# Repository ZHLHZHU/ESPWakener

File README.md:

## 简介
EspWakener是一个基于Wake-on-LAN协议的网络唤醒器，通过MQTT协议进行控制。

## 配置说明
* 把开关拨到"ON"，通电（顺序不能乱）。连上Wakener发出的热点，进入192.168.8.1（你都看到本页面了，肯定已经完成这些步骤）。
* 进入Config页签，配置好WIFI名和密码、WOL的端口（默认9）。
* 打开MQTT开关，填入MQTT连接（只支持mqtt://协议，不支持TLS和WS），填入Topic。MQTT用户名和密码如果没有可以忽略。
* 点击保存，把开关拨到"1"，断电，通电。（拨开关和断电的顺序任意，因为本设备只会根据通电瞬间的开关状态来判断是否进入配置模式）。
## 协议
### Wakener上线
当Wakener成功连接Mqtt服务器后，会广播一条自身状态的信息
```json
{
    "action": "join",
    "sender": "SwingFrogWakener",
    "deviceName": "SwingFrogWakener",
    "ip": "192.168.1.188",
    "ssid": "WIFI_NAME",
    "rssi": -47,
    "version": "2.0.0"
}
```
### 请求唤醒
向Wakener所配置的Topic发送以下指令，Wakener将会在所在局域网广播唤醒包
MAC地址分隔符支持 ':' 和 '-'
```json
{
    "action": "wake",
    "mac": "a9:a9:59:30:d8:ee"
}
```
### 请求设备状态
向Wakener所配置的Topic发送以下指令，将会返回Wakener当前状态信息
```json
{
    "action": "info"
}
```

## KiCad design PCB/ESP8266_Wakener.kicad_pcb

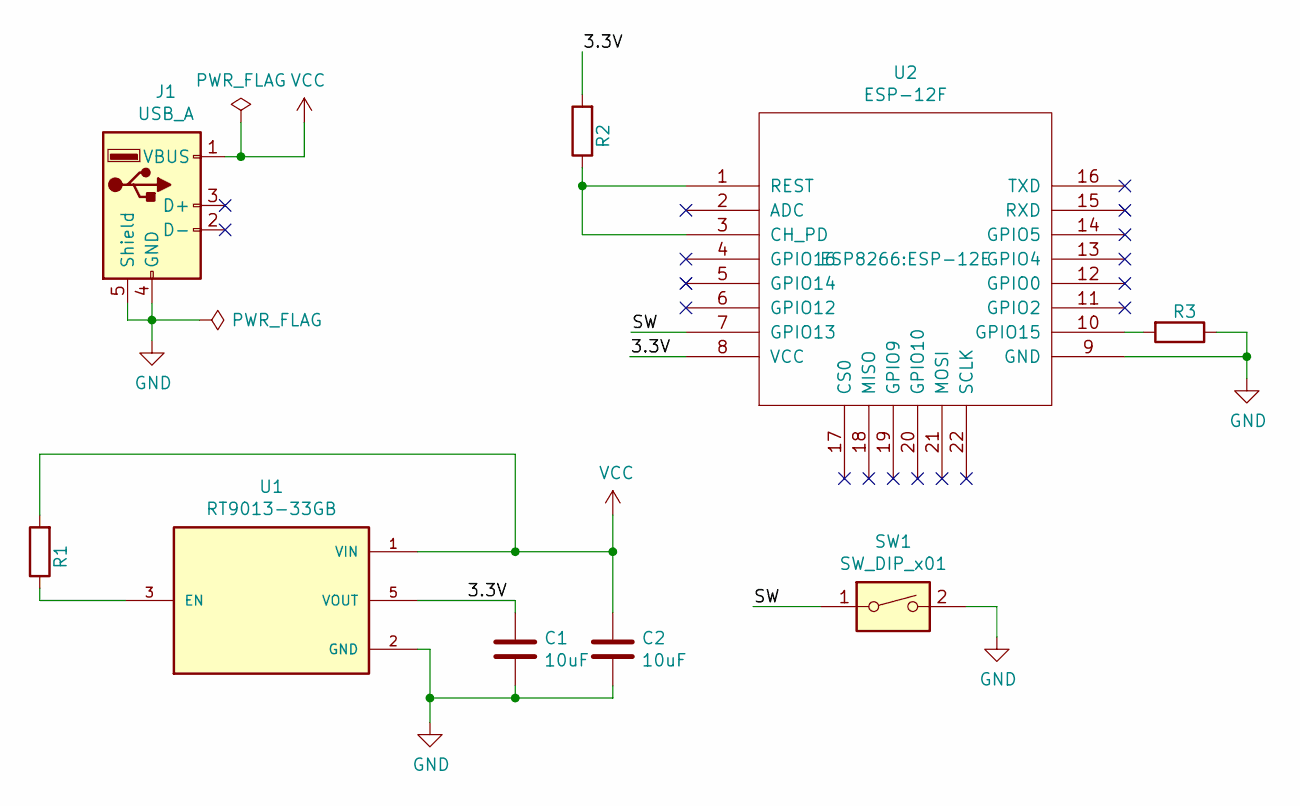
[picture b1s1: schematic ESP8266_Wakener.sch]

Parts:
C1, C2: 10uF; C_0603_1608Metric
J1: USB_A; USB_A_CNCTech_1001-011-01101_Horizontal
R1, R2, R3: 10K; R_0603_1608Metric
SW1: SW_DIP_x01; SW_SMT_1P
U1: RT9013-33GB; SOT-23-5_HandSoldering; PARTREV Aprill 2011
U2: ESP-12F; ESP-12E

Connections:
/3.3V: C1.1, R2.2, U1.5 (VOUT), U2.8 (VCC)
/SW: SW1.1, U2.7 (GPIO13)
GND: C1.2, C2.2, J1.4 (GND), J1.5 (Shield), R3.1, SW1.2, U1.2 (GND), U2.9 (GND)
unnamed: R1.1, U1.3 (EN)
unnamed: R2.1, U2.1 (REST), U2.3 (CH_PD)
unnamed: R3.2, U2.10 (GPIO15)
VCC: C2.1, J1.1 (VBUS), R1.2, U1.1 (VIN)

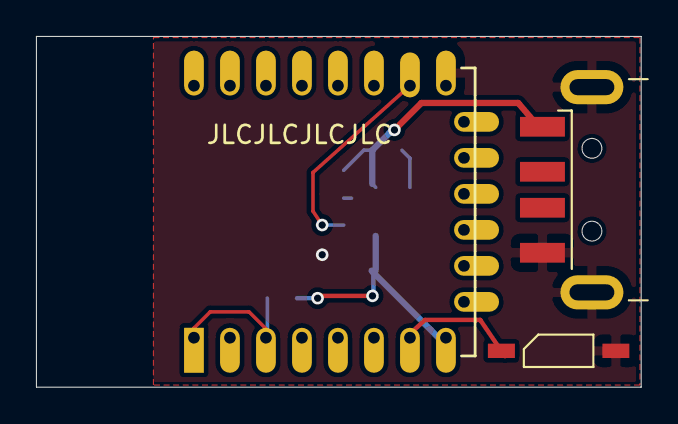
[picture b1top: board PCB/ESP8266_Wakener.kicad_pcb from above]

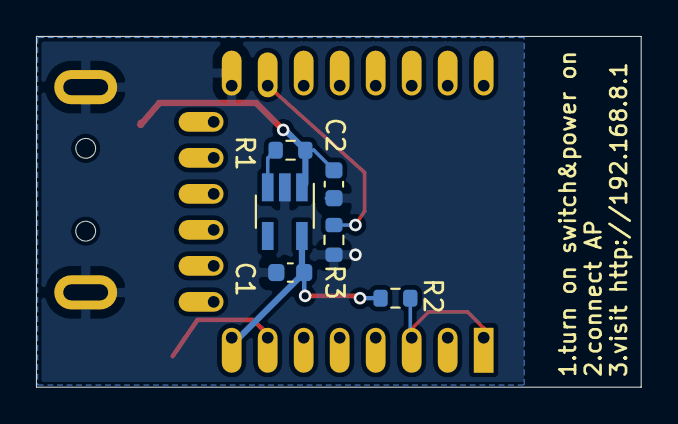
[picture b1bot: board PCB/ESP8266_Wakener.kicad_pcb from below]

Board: 2 copper layers, 33.6 x 19.5 mm, 9 parts (6 on the bottom side), 7 nets.

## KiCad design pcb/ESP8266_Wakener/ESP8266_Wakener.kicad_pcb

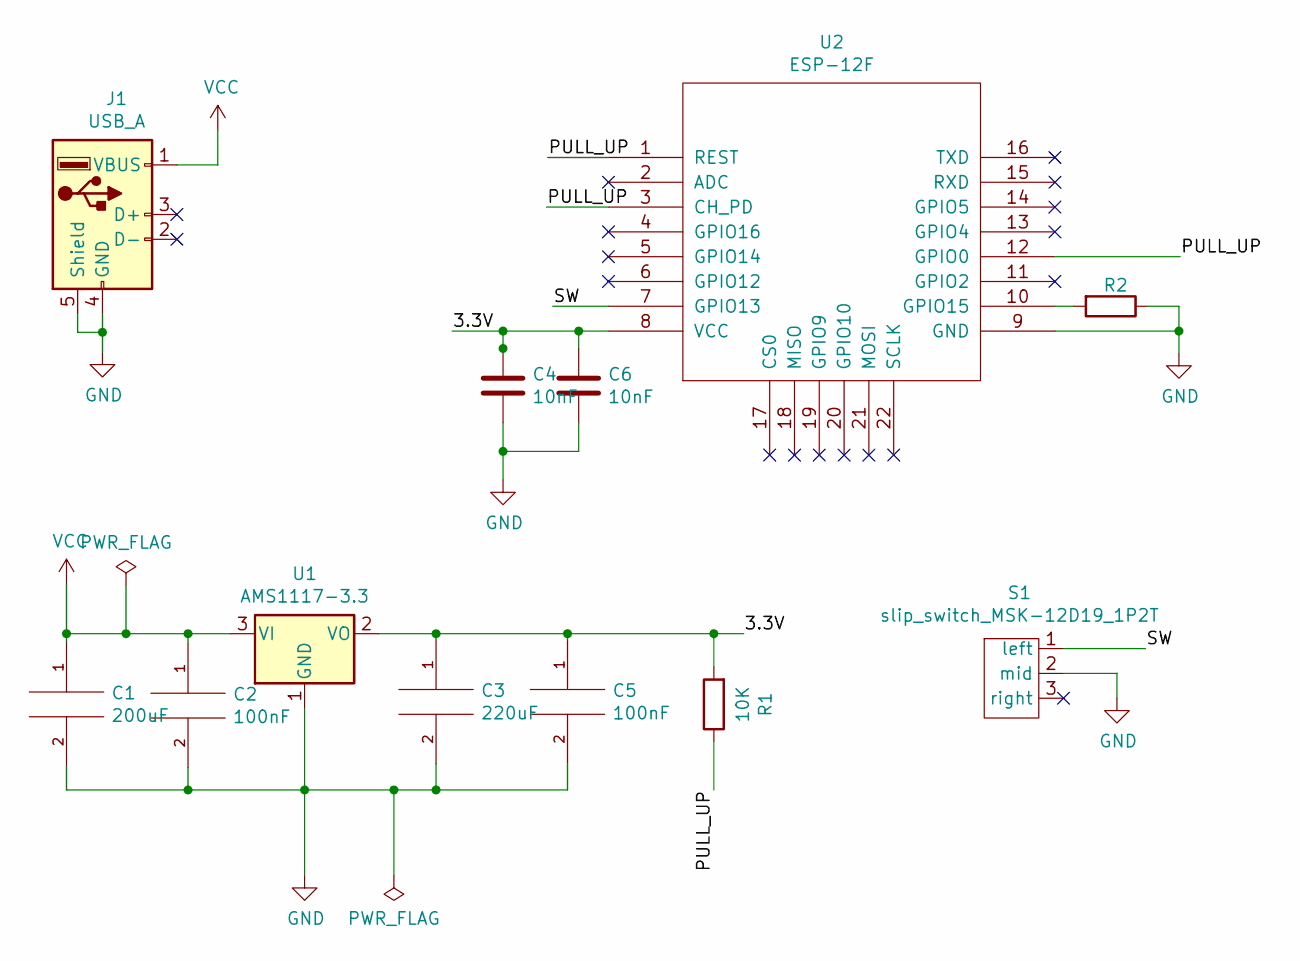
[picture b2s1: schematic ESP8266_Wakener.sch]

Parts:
C1: 200uF; C_0603_1608Metric
C2, C5: 100nF; C_0603_1608Metric
C3: 220uF; C_0603_1608Metric
C4, C6: 10nF; C_0603_1608Metric
J1: USB_A; USB_A_CNCTech_1001-011-01101_Horizontal
R1, R2: 10K; R_0603_1608Metric
S1: slip_switch_MSK-12D19_1P2T; SlipSwitch_MSK-12D19_1P2T
U1: AMS1117-3.3; SOT-223-3_TabPin2
U2: ESP-12F; ESP-12E

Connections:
/3.3V: C3.1, C4.1, C5.1, C6.1, R1.2, U1.2 (VO), U2.8 (VCC)
/PULL_UP: R1.1, U2.1 (REST), U2.3 (CH_PD), U2.12 (GPIO0)
/SW: S1.1 (left), U2.7 (GPIO13)
GND: C1.2, C2.2, C3.2, C4.2, C5.2, C6.2, J1.4 (GND), J1.5 (Shield), R2.1, S1.2 (mid), U1.1 (GND), U2.9 (GND)
unnamed: R2.2, U2.10 (GPIO15)
VCC: C1.1, C2.1, J1.1 (VBUS), U1.3 (VI)

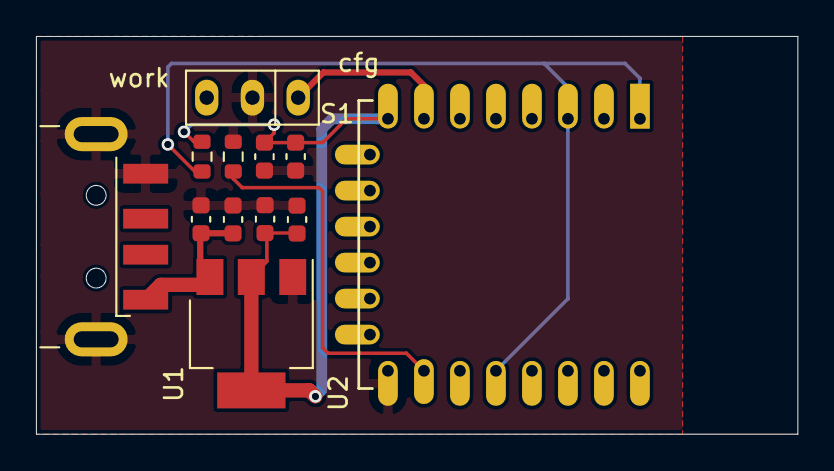
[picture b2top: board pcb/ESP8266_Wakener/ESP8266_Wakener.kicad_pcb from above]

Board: 2 copper layers, 42.3 x 22.1 mm, 12 parts (0 on the bottom side), 6 nets.

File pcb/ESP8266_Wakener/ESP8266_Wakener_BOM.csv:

"Comment","Description","Designator","Footprint","LibRef","Pins","Quantity","PartNumber","url",
"200uF","desc","C1,","C_0603_1608Metric","libref","2","1","","",
"100nF","desc","C2,C5,","C_0603_1608Metric","libref","2","2","","",
"220uF","desc","C3,","C_0603_1608Metric","libref","2","1","","",
"10nF","desc","C4,C6,","C_0603_1608Metric","libref","2","2","","",
"10K","desc","R1,R2,","R_0603_1608Metric","libref","2","2","","",
"AMS1117-3.3","desc","U1,","SOT-223-3_TabPin2","libref","4","1","","",
"Through Hole Items ",
"USB_A","desc","J1,","USB_A_CNCTech_1001-011-01101_Horizontal","libref","8","1","","",
"slip_switch_MSK-12D19_1P2T","desc","S1,","SlipSwitch_MSK-12D19_1P2T","libref","3","1","","",
"ESP-12F","desc","U2,","ESP-12E","libref","22","1","","",

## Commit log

2021-10-19 add ignore rule
2021-10-19 init
2021-10-19 Update README.md
    typo
2021-10-19 update config page
2021-10-19 fix typo
